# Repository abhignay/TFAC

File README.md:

# TFAC

Symbols and Footprints will be added soon

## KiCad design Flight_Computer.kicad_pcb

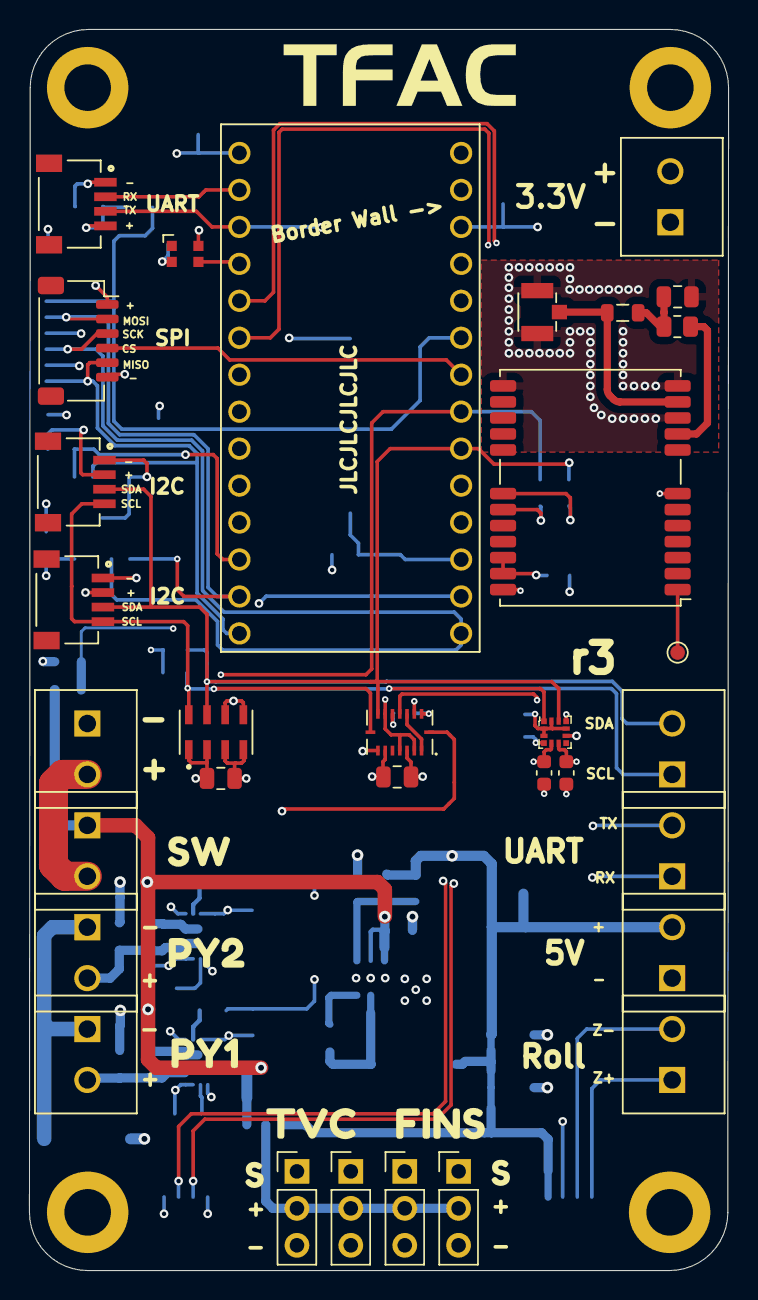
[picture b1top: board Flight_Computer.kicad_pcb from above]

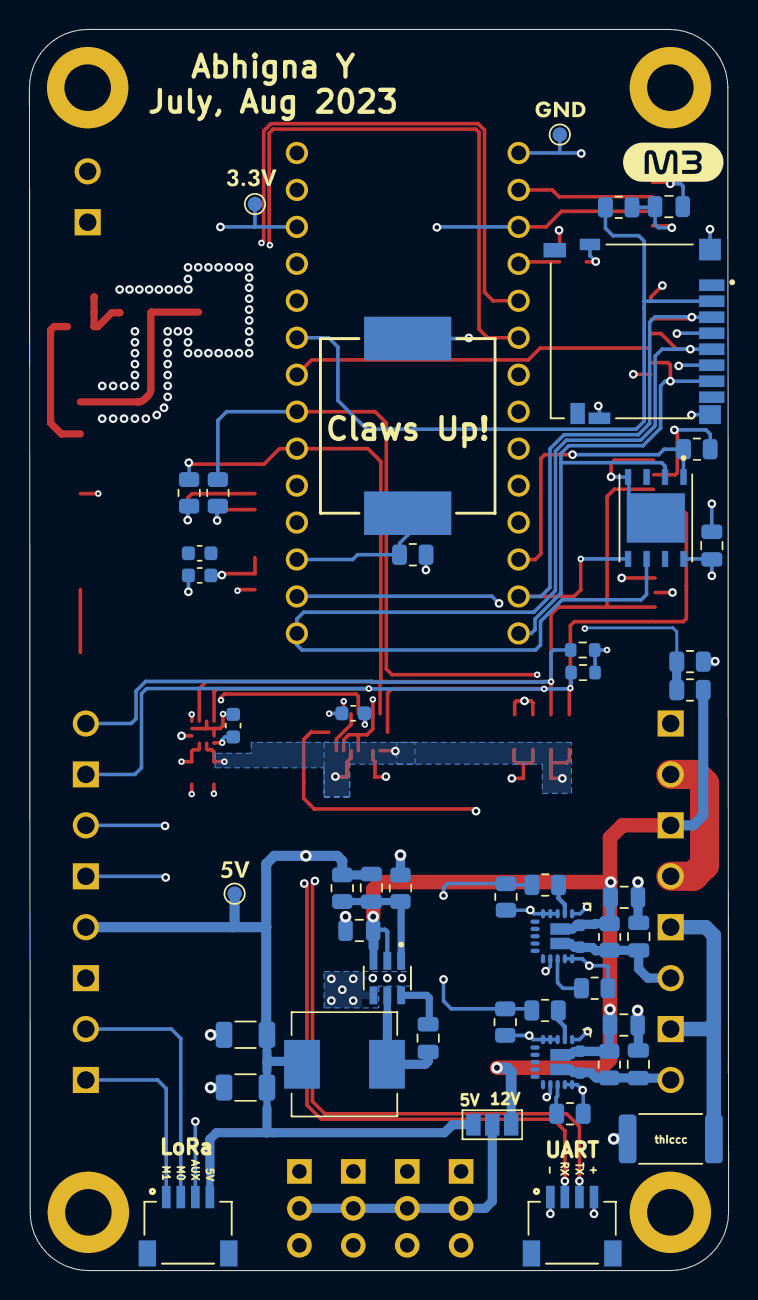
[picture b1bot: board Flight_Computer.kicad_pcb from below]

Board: 4 copper layers, 48.0 x 85.3 mm, 96 parts (52 on the bottom side), 48 nets.

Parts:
B1: AST1240MLQTR; AST1240MLTRQ
C1, C2, C5, C14: 0.1uF; C_0603_1608Metric
C3, C4: 1uF; C_0603_1608Metric
C6, C8: 47pF; C_0805_2012Metric
C7, C10, C15, C25, C26, C27, C28: 10uF; C_0805_2012Metric
C12, C13, C17: 0.1uF; C_0805_2012Metric
C20, C21: 22uF; C_1206_3216Metric
D1: NeoPixel; WS2812B-2020_2x2mm
H1, H2, H3, H4: MountingHole; MountingHole_3.2mm_M3_DIN965_Pad
HD1, HD2, HD4, HD5, HD6: Header_1x4; JST_SM04B-SRSS-TB(LF)(SN)
J1, J2, J3, J4, J6: Screw_Terminal_01x02; OST_OSTTE020104
JP1: SolderJumper_3_Open; SolderJumper-3_P1.3mm_Open_Pad1.0x1.5mm
L1: 6.8uH; SRP7028A-6R8M
L2: 27nH; L_0805_2012Metric
M1, M2, M3, M4: Motor_Servo; PinHeader_1x03_P2.54mm_Vertical
R1, R2: 33ohm; R_0805_2012Metric
R3: 10ohm; R_0805_2012Metric
R4, R17, R18: 1k; R_0805_2012Metric
R5, R7, R14, R15: 10k; R_0805_2012Metric
R6, R8: 4.7k; R_0603_1608Metric
R10, R11: 470ohm; R_0805_2012Metric
R12, R13: 47ohm; R_0805_2012Metric
R19: 4.7ohm; R_2512_6332Metric
R24: 158k; R_0805_2012Metric
R25, R27: 30.1k; R_0805_2012Metric
R26: 86.6k; R_0805_2012Metric
TM1: Battery_Term; OST_OSTTE020104
TM2: Switch; OST_OSTTE020104
TM3, TM8: Screw_Terminal_01x02; OST_OSTTE020104
TP1: Safeboot-GND; TestPoint_Pad_D1.0mm
TP2, TP3, TP4: TEST-POINT; TestPoint_Pad_D1.0mm
U1: LIS3MDL; VFLGA-12_2x2mm
U2: AP63301WU-7
U3: Teensy4.0; Teensy_4.0
U4: NEO-M8N; ublox_NEO
U5: IS25LP064A-JKLE
U6: UFL_Conn; UFL
U7: BMI088; BMI088_usethisboi_QFN_Package
U8: MS5611
U9: JST6Pin; JST_SH_SM06B-SRSS-TB_1x06-1MP_P1.00mm_Horizontal
U10: DM3D-SF; HRS_DM3D-SF
U12, U13: UCS3205
kibuzzard-616AC14D, kibuzzard-616AC14D#2, kibuzzard-6177BE78, kibuzzard-6177C39A, kibuzzard-6177F1EE: G***; label
kibuzzard-630E12E2: G***; kibuzzard-630E12E2
kibuzzard-630E342B: G***; kibuzzard-630E342B
kibuzzard-630E1258: G***; kibuzzard-630E1258
kibuzzard-630E3421: G***; kibuzzard-630E3421
kibuzzard-630E3438: G***; kibuzzard-630E3438
kibuzzard-648440F5: G***; kibuzzard-648440F5
kibuzzard-64844101: G***; kibuzzard-64844101

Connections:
+3V3: C2.1, C3.1, C5.1, C7.1, C10.1, C12.1, C13.1, C14.1, D1.4 (VDD), HD1.4, HD2.2, HD4.2, HD6.4, J3.2, R5.1, R6.2, R7.1, R8.2, TP3.1, U1.5 (VDD), U1.6 (VDDIO), U1.10 (CS), U3.24 (3.3V), U4.22 (V_BCKP), U4.23 (VCC), U5.8 (VCC), U7.3 (VDD), U7.7 (PS), U7.11 (VDDIO), U7.14 (CSB1), U8.1 (VDD), U8.2 (PS), U9.1, U10.4 (VDD), U12.12 (LATCH), U13.12 (LATCH)
+5V: C8.1, C20.1, C21.1, HD5.4, J6.2, JP1.1 (A), L1.2, R24.1, TP2.1, U3.VIN
+12V: C15.1, C25.1, C26.1, JP1.3 (B), R14.2, R15.2, R26.1, TM2.1, U2.2 (EN), U2.3 (VIN), U12.19 (VIN), U12.20 (VOUT), U12.22 (VIN), U13.19 (VIN), U13.20 (VOUT), U13.22 (VIN)
/BATT: TM1.2, TM2.2
/Flash_SD_Card/FLASH-CS: R5.2, U3.10 (CS), U5.1 (CS)
/Flash_SD_Card/MISO: U3.12 (MISO), U5.2 (MISO), U9.5, U10.7 (DAT0/MISO)
/Flash_SD_Card/MOSI: U3.11 (MOSI), U5.5 (MOSI), U9.2, U10.3 (CMD/MOSI)
/Flash_SD_Card/SCK: U3.13 (SCK/LED), U5.6 (SCK), U9.3, U10.5 (CLK)
/Flash_SD_Card/SD-CS: R7.2, U3.21 (A7/RX), U10.2 (DAT3/CS)
/GNSS_Radio/GNSS_ANT: L2.1, U4.11 (RF_IN), U6.1
/GNSS_Radio/SCL: HD2.4, HD4.4, J2.1, R2.2, R6.1, U1.1 (SCL), U3.19 (A5/SCL), U7.8 (SCL), U8.8 (SCLK)
/GNSS_Radio/SDA: HD2.3, HD4.3, J2.2, R1.2, R8.1, U1.11 (SDA), U3.18 (A4/SDA), U7.9 (SDA), U8.7 (SDA)
/GNSS_Radio/VREF_GNSS: R3.2, U4.9 (VCC_RF)
/Peripherals+Outputs/Buzz: B1.1 (+), R4.1, U3.15 (A1/RX)
/Peripherals+Outputs/CS: U3.20 (A6/TX), U9.4
/Peripherals+Outputs/FIN1: HD5.3, M4.1 (PWM), U3.5 (IN2/PWM)
/Peripherals+Outputs/FIN2: M3.1 (PWM), U3.6 (OUT1D/PWM)
/Peripherals+Outputs/NEO-PIX: D1.3 (DIN), U3.2 (OUT2/PWM)
/Peripherals+Outputs/RX: HD1.2, HD6.2, J4.1, U3.0 (RX1/PWM)
/Peripherals+Outputs/Servo_PWR: JP1.2 (C), M1.2 (+), M2.2 (+), M3.2 (+), M4.2 (+)
/Peripherals+Outputs/TVCX: M2.1 (PWM), U3.7 (RX2/PWM)
/Peripherals+Outputs/TVCY: M1.1 (PWM), U3.8 (TX2/PWM)
/Peripherals+Outputs/TX: HD1.3, HD6.3, J4.2, U3.1 (TX1/PWM)
/Peripherals+Outputs/Z+: HD5.1, J1.1, U3.4 (BCLK2/PWM)
/Peripherals+Outputs/Z-: HD5.2, J1.2, U3.3 (LRCLK2/PWM)
/Power_Input_Regulator/VOLTAGE: R26.2, R27.1, U3.14 (A0/TX)
/Proc/Accel_INT: U3.9 (OUT1C/PWM), U7.16 (INT1)
/Proc/Gyro_INT: U3.16 (A2/SCL1), U7.12 (INT3)
/Proc/Mag_INT: U1.8 (DRDY), U3.17 (A3/SDA1)
/Proc/PY1: R10.2, R12.2, U3.23 (A9/CRX1)
/Proc/PY2: R11.2, R13.2, U3.22 (A8/CTX1)
/PyroTechnic_Channels/-: R19.2, TM3.1, TM8.1
/PyroTechnic_Channels/VOUT1: C27.1, R14.1, TM8.2, U12.16 (VOUT), U12.17 (VOUT), U12.21 (VOUT)
/PyroTechnic_Channels/VOUT2: C28.1, R15.1, TM3.2, U13.16 (VOUT), U13.17 (VOUT), U13.21 (VOUT)
GND: B1.2 (-), C1.2, C2.2, C3.2, C5.2, C6.2, C7.2, C10.2, C12.2, C13.2, C14.2, C15.2, C20.2, C21.2, C25.2, C26.2, C27.2, C28.2, D1.2 (VSS), HD1.1, HD2.1, HD4.1, HD6.1, J3.1, J6.1, M1.3 (-), M2.3 (-), M3.3 (-), M4.3 (-), R4.2, R10.1, R11.1, R17.1, R18.1, R19.1, R25.2, R27.2, TM1.1, TP4.1, U1.2 (RES), U1.3 (GND), U1.9 (SDO), U1.12 (RES), U2.4 (GND), U3.G1 (GND), U3.G3 (GND), U4.7 (VDD_USB), U4.10 (GND), U4.12 (GND), U4.13 (GND), U4.24 (GND), U5.4 (GND), U5.9 (GND), U6.2, U7.2 (NC), U7.4 (GND), U7.6 (GNDIO), U7.10 (SDO2), U7.15 (SDO1), U8.3 (GND), U8.4 (CSB), U8.5 (CSB), U8.6 (SDO), U9.6, U10.6 (VSS), U10.S1 (GND4), U10.S2 (GND3), U10.S3 (GND1), U10.S4 (GND2), U12.1 (GND), U12.3 (FRS), U12.4 (DIR), U12.5 (DSC), U12.14 (VOV), U12.15 (GND), U13.1 (GND), U13.3 (FRS), U13.4 (DIR), U13.5 (DSC), U13.14 (VOV), U13.15 (GND)
unnamed: C6.1, L2.2, R3.1
unnamed: C1.1, U1.4 (C1)
unnamed: C17.1, U2.6 (BST)
unnamed: C8.2, R24.2, R25.1, U2.1 (FB)
unnamed: C17.2, L1.1, U2.5 (SW)
unnamed: R2.1, U4.19 (SCL/SPI_CLK)
unnamed: R1.1, U4.18 (SDA/~SPI_CS)
unnamed: TP1.1, U4.1 (~SAFEBOOT)
unnamed: U7.1 (INT2), U7.13 (INT4)
unnamed: R12.1, U12.2 (EN)
unnamed: R17.2, U12.13 (ISEN)
unnamed: R13.1, U13.2 (EN)
unnamed: R18.2, U13.13 (ISEN)
